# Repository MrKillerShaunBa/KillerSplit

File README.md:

# KillerSplit

An ergonomic, wireless, split, low-profile keyboard. This is a fusion between a Corne and a ZMK Voyager. It has a 6-column layout like the Corne, but the thumb buttons are placed like a Voyager.
I got the inspiration and motivation after looking at so many cool designs in r/ErgoMechKeyboards so wanted to make one of my own.

Link to demo-[https://www.youtube.com/shorts/nLBKlfsz7i4](https://www.youtube.com/shorts/nLBKlfsz7i4)

## Features

- Column staggered
- Ortholinear
- 42 keys
- Low profile Choc Tactile Switches
- Wireless
- ZMK Firmware
- Hotswappable

## CAD
Left | Right
:---:|:---:
 | 

## PCB

Left | Right
:---:|:---:
 | 

## ZMK Keymap

### BOM

| Product | Quantity | Source | Price(INR) | Price($) | Link |
| :-----: | :-----: | :-----: | :-----: | :-----: | :-----: |
| Kailh Choc Low Profile Switches | 50 | Typeractive | - | 27.5 | [here](https://typeractive.xyz/products/choc-switches?variant=51038935122151) |
| Battery Jack | 2 | Typeractive | - | 2 | [here](https://typeractive.xyz/products/battery-jack?variant=46024892186855) |
| Reset Button | 2 | Typeractive | - | 1.50 | [here](https://typeractive.xyz/products/reset-button?variant=45597784932583) |
| Power Switch | 2 | Typeractive | - | 1.50 | [here](https://typeractive.xyz/products/power-switch?variant=45597854171367) |
| Choc hotswap Sockets | 50 | Typeractive | - | 7.50 | [here](https://typeractive.xyz/products/hotswap-sockets?variant=45742200324327) |
| MBK Choc Keycaps 1.5u | 2 | Typeractive | - | 1.50 | [here](https://typeractive.xyz/products/mbk-keycaps?variant=45419753210087) |
| MBK Choc Keycaps 1u | 40 | Typeractive | - | 12 | [here](https://typeractive.xyz/products/mbk-keycaps?variant=45419753079015) |
| Tenting Feet | 4 | Typeractive | - | 15 | [here](https://typeractive.xyz/products/tenting-feet) |
| Lithium Battery 110mah | 2 | Typeractive | - | 8 | [here](https://typeractive.xyz/products/lithium-battery-110mah?variant=46118748291303) |
| Mill-Max Sockets and Pins (12 pin) | 2 sets | Typeractive | - | 13 | [here](https://typeractive.xyz/products/machine-sockets-and-pins?variant=45741664469223) |
| Choc Switch Opener | 1 | Typeractive | - | 3 | [here](https://typeractive.xyz/products/switch-opener?variant=45535960662247) |
| PCB Left | 5 | JLCPCB | - | 10.90 | - |
| PCB Right | 5 | JLCPCB | - | 10.90 | - |
| JLC Shipping | - | JLCPCB | - | 22.73 | - |
| JLC Discount | - | JLCPCB | - | -20 | - |
| Case and Plates | - | Print Legion | - | ~5 | Only Shipping |
| ProMicro nrf52840 Board | 2 | Probots | 1,417 | 16.50 | (Includes Shipping)[here](https://probots.co.in/pro-micro-nrf52840-development-board-compatible-with-nice-nano-v2-0.html) |
| Diodes 1n4148 | 5*10 | StacksKB | 75 | 0.85 | [here](https://stackskb.com/store/1n4148-through-hole-diode/) |
| Oled Display 0.91inch I2C | 2 | Probots | 598 | 7.6 | [here](https://probots.co.in/0-91-oled-display-white-128x32-for-arduino-raspberry-pi-i2c.html) |
| M2 Standoff and Screws (Assorted) | 10 sets | StacksKB | 421 | 4.8 | (10x5mm standoff, 10x5mm screw, 10x8mm screw)[here](https://stackskb.com/product-category/parts/fasteners/) |

Total (using coupon)= $152

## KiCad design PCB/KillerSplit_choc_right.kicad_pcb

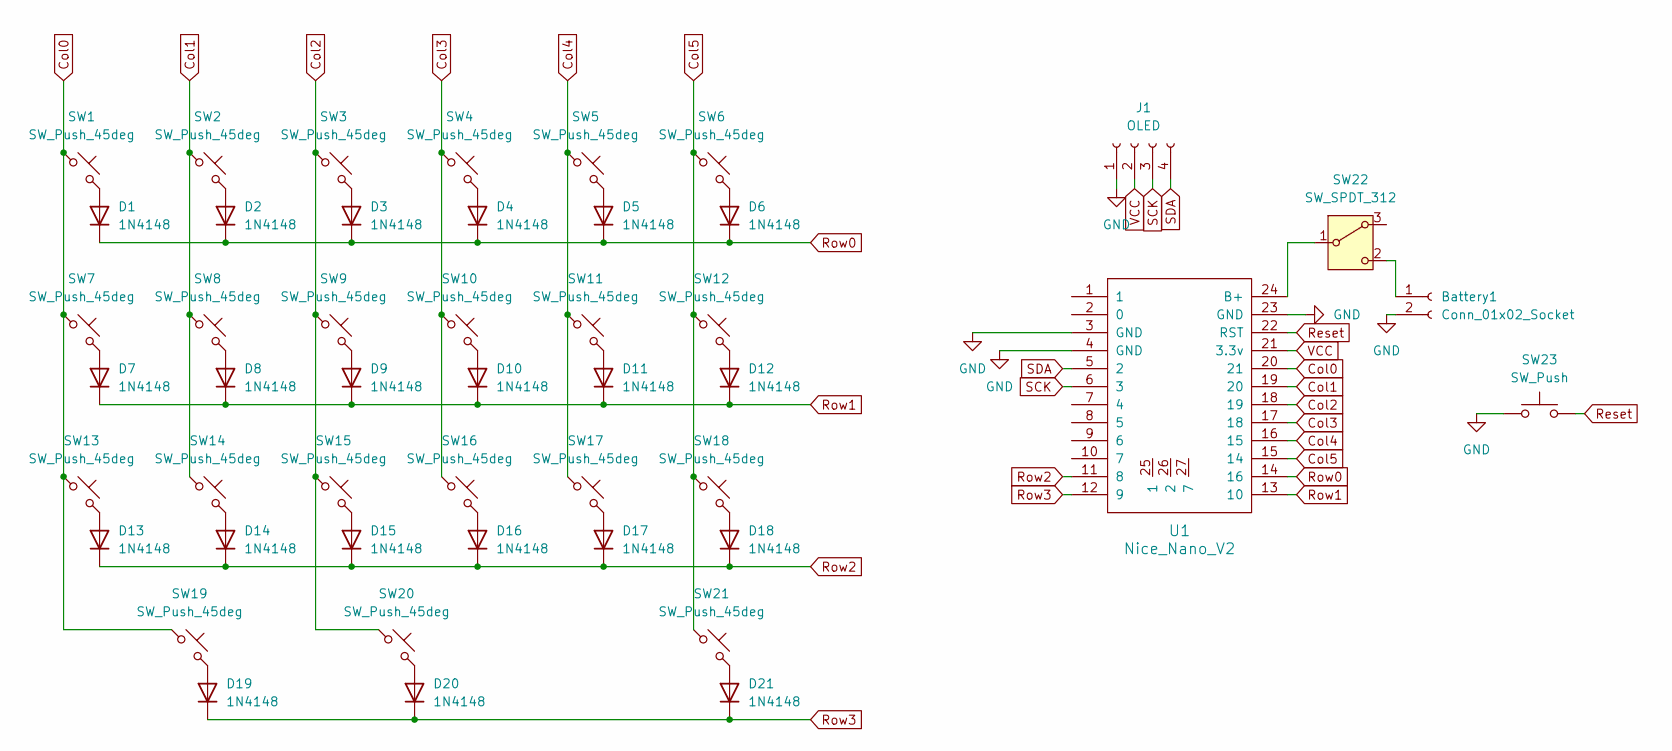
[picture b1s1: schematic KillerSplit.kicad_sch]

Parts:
Battery1: Conn_01x02_Socket; JST_PH_S2B-PH-K_1x02_P2.00mm_Horizontal
D1, D2, D3, D4, D5, D6, D7, D8, D9, D10, D11, D12, D13, D14, D15, D16, D17, D18, D19, D20, D21: 1N4148; D_DO-35_SOD27_P7.62mm_Horizontal
J1: OLED; SSD1306-0.91-OLED-4pin-128x32_3d
SW1, SW2, SW3, SW4, SW5, SW6, SW7, SW8, SW9, SW10, SW11, SW12, SW13, SW14, SW15, SW16, SW17, SW18, SW19, SW20: SW_Push_45deg; Hotswap_Choc_V1V2_Plated_1.00u_plate_cutout
SW21: SW_Push_45deg; Hotswap_Choc_V1V2_Plated_1.50u_plate_cutout
SW22: SW_SPDT_312; SW_SPDT_PCM12
SW23: SW_Push; Panasonic_EVQPUL_EVQPUC
U1: Nice_Nano_V2; Nice_Nano_V2_Flipped

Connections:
Col0: SW1.1, SW7.1, SW13.1, SW19.1, U1.20 (21)
Col1: SW2.1, SW8.1, SW14.1, U1.19 (20)
Col2: SW3.1, SW9.1, SW15.1, SW20.1, U1.18 (19)
Col3: SW4.1, SW10.1, SW16.1, U1.17 (18)
Col4: SW5.1, SW11.1, SW17.1, U1.16 (15)
Col5: SW6.1, SW12.1, SW18.1, SW21.1, U1.15 (14)
GND: Battery1.2, J1.1, SW23.1, U1.3 (GND), U1.4 (GND), U1.23 (GND)
unnamed: Battery1.1, SW22.2 (C)
unnamed: D1.2 (A), SW1.2
unnamed: D2.2 (A), SW2.2
unnamed: D3.2 (A), SW3.2
unnamed: D4.2 (A), SW4.2
unnamed: D5.2 (A), SW5.2
unnamed: D6.2 (A), SW6.2
unnamed: D7.2 (A), SW7.2
unnamed: D8.2 (A), SW8.2
unnamed: D9.2 (A), SW9.2
unnamed: D10.2 (A), SW10.2
unnamed: D11.2 (A), SW11.2
unnamed: D12.2 (A), SW12.2
unnamed: D13.2 (A), SW13.2
unnamed: D14.2 (A), SW14.2
unnamed: D15.2 (A), SW15.2
unnamed: D16.2 (A), SW16.2
unnamed: D17.2 (A), SW17.2
unnamed: D18.2 (A), SW18.2
unnamed: D19.2 (A), SW19.2
unnamed: D20.2 (A), SW20.2
unnamed: D21.2 (A), SW21.2
unnamed: SW22.1 (B), U1.24 (B+)
Reset: SW23.2, U1.22 (RST)
Row0: D1.1 (K), D2.1 (K), D3.1 (K), D4.1 (K), D5.1 (K), D6.1 (K), U1.14 (16)
Row1: D7.1 (K), D8.1 (K), D9.1 (K), D10.1 (K), D11.1 (K), D12.1 (K), U1.13 (10)
Row2: D13.1 (K), D14.1 (K), D15.1 (K), D16.1 (K), D17.1 (K), D18.1 (K), U1.11 (8)
Row3: D19.1 (K), D20.1 (K), D21.1 (K), U1.12 (9)
SCK: J1.3, U1.6 (3)
SDA: J1.4, U1.5 (2)
VCC: J1.2, U1.21 (3.3v)

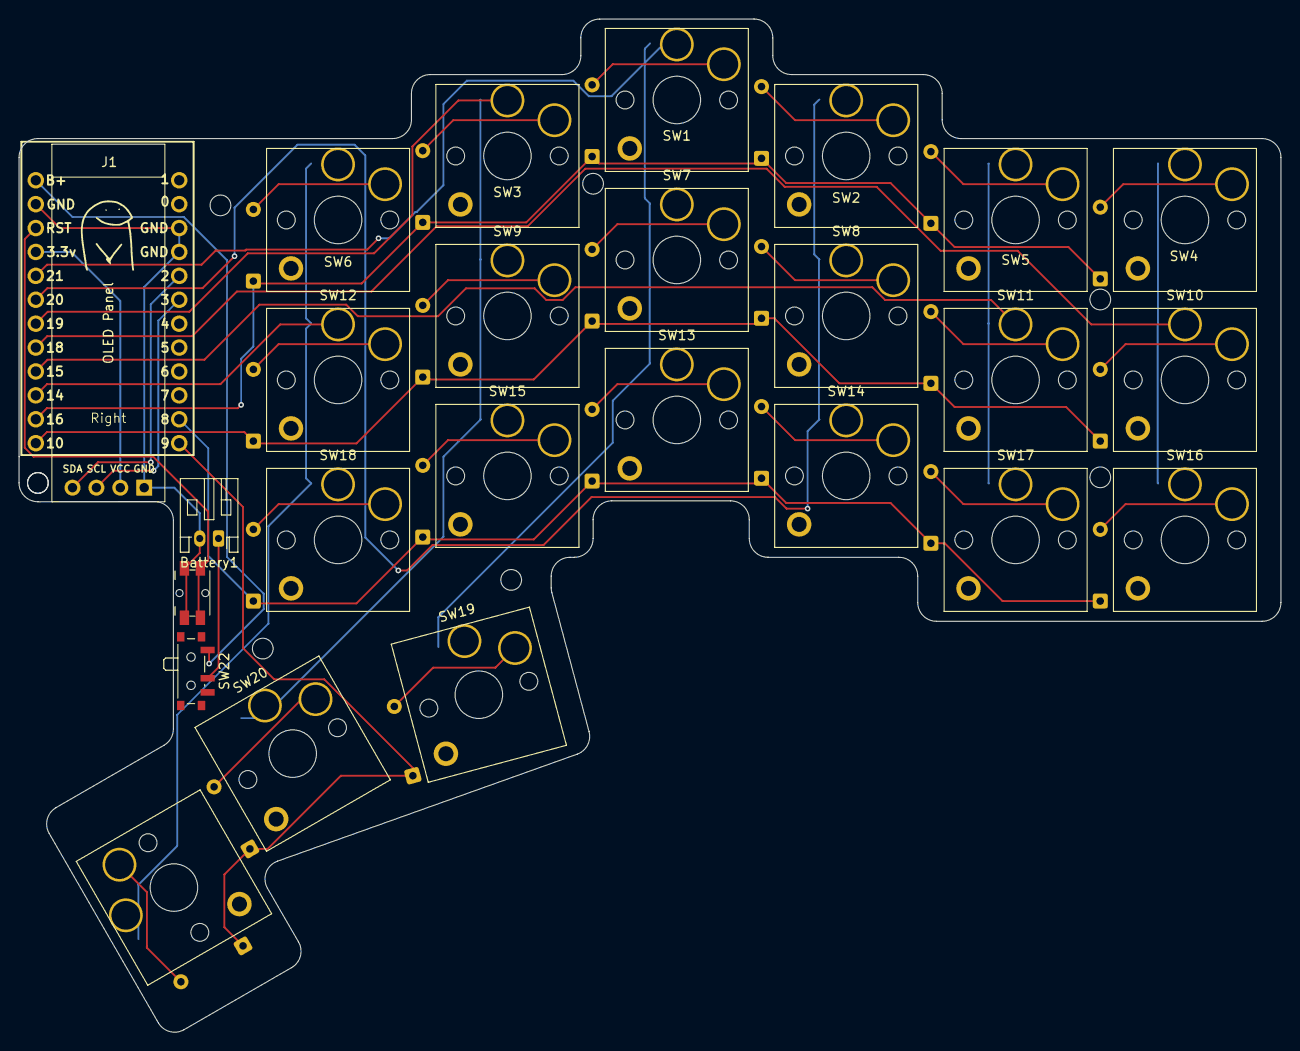
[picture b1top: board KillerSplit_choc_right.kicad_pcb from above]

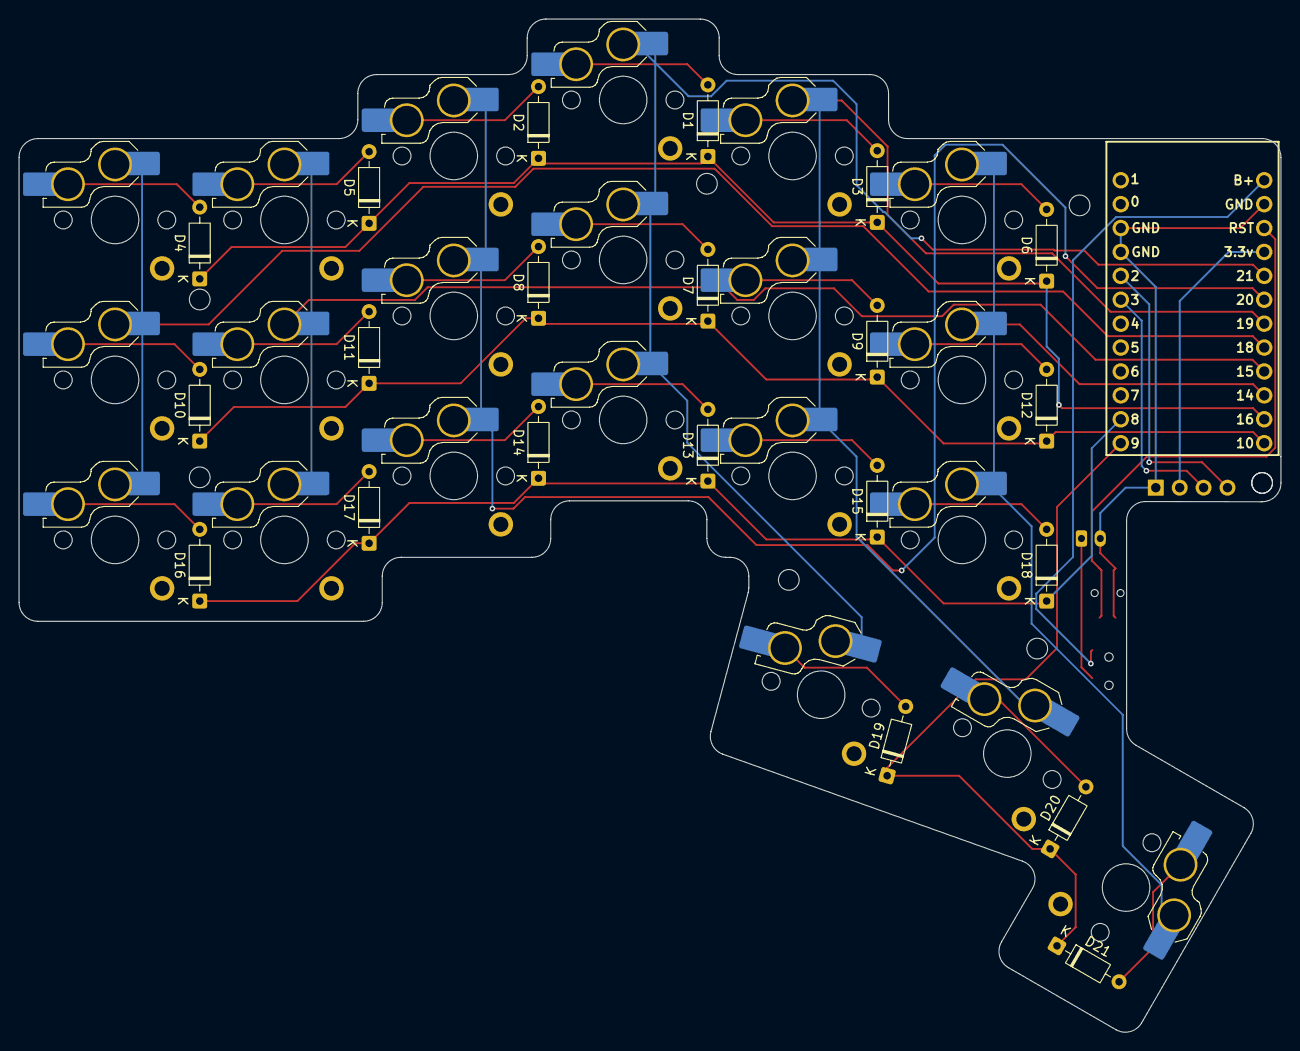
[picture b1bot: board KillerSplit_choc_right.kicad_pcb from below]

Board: 2 copper layers, 134.1 x 107.7 mm, 47 parts (21 on the bottom side), 38 nets.

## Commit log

2025-12-27 Update README with demo link and images
    Added demo link and images to README.
